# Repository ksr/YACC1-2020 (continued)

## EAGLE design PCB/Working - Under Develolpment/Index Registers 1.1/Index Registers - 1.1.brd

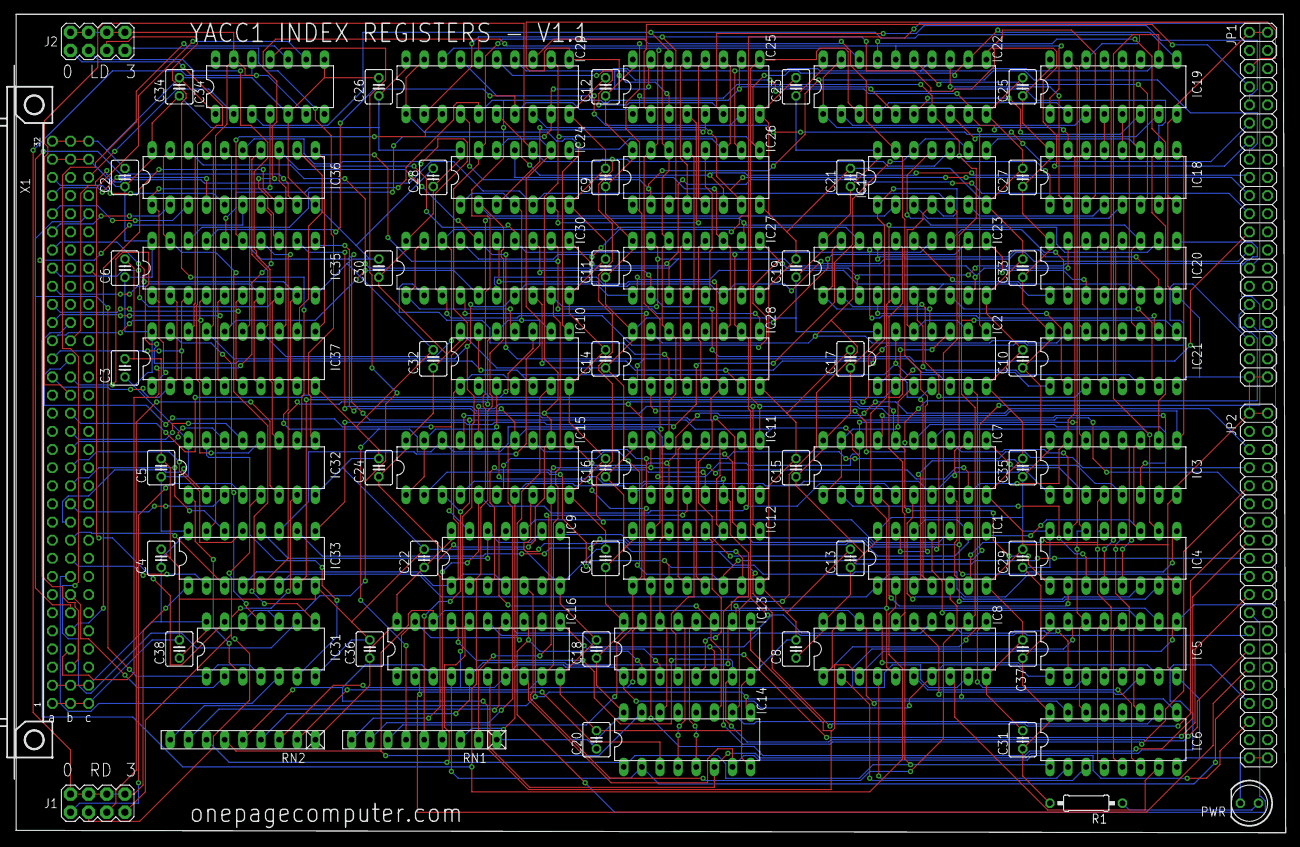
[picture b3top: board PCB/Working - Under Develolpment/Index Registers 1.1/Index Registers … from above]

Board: 2 copper layers, 177.8 x 114.6 mm, 83 parts (0 on the bottom side), 192 nets.

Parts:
C1, C2, C3, C4, C5, C6, C8, C9, C10, C11, C12, C13, C14, C15, C16, C17, C18, C19, C20, C21, C22, C23, C24, C25, C26, C27, C28, C29, C30, C31, C32, C33, C34, C35, C36, C37, C38: 0.1; C025-040X050
IC1, IC2, IC9, IC10, IC17, IC24, IC31: 74LS32N; DIL14
IC3, IC4, IC5, IC6, IC11, IC12, IC13, IC14, IC18, IC19, IC20, IC21, IC25, IC26, IC27, IC28: 74LS192N; DIL16
IC7, IC8, IC15, IC16, IC22, IC23, IC29, IC30: 74LS244N; DIL20
IC32, IC33: 74LS139N; DIL16
IC34: 4077N; DIL14
IC35, IC36, IC37: 74LS245N; DIL20
J1, J2: 2X4
JP1, JP2: 2X20
PWR: LED5MM
R1: 330; 0207/10
RN1, RN2: 10k; RN-9
X1: FABC96R

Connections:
-BUS-EN: IC31.1, IC31.4, X1.C28
-HL-SWAP: IC31.13, IC34.9, X1.C25
-LDSEL: IC33.15, IC34.6, IC34.13, J2.2, J2.4, J2.6, J2.8
-R0-LDSEL: IC9.9, IC9.12, IC33.12
-R0-RDSEL: IC9.1, IC9.4, IC10.1, IC10.4, IC33.4
-R1-LDSEL: IC24.9, IC24.12, IC33.11
-R1-RDSEL: IC10.9, IC10.12, IC24.1, IC24.4, IC33.5
-R2-LDSEL: IC1.9, IC1.12, IC33.10
-R2-RDSEL: IC1.1, IC1.4, IC2.1, IC2.4, IC33.6
-R3-LDSEL: IC17.9, IC17.12, IC33.9
-R3-RDSEL: IC2.9, IC2.12, IC17.1, IC17.4, IC33.7
-RDSEL: IC33.1, IC34.12, J1.2, J1.4, J1.6, J1.8
-REG-DN: IC1.5, IC9.5, IC17.5, IC24.5, X1.B21
-REG-FUNC-LD: IC31.5, X1.B8
-REG-FUNC-RD: IC31.2, X1.B7
-REG-LD-HI: IC1.13, IC9.13, IC17.13, IC24.13, X1.B20
-REG-LD-LO: IC1.10, IC9.10, IC17.10, IC24.10, X1.B18
-REG-RD-HI: IC2.5, IC2.13, IC10.5, IC10.13, X1.B19
-REG-RD-LO: IC2.2, IC2.10, IC10.2, IC10.10, X1.B17
-REG-UP: IC1.2, IC9.2, IC17.2, IC24.2, X1.B22
-RESET: IC34.2, X1.C30
-RLD0: IC32.12, J2.1
-RRD0: IC32.4, J1.1
ADATA0: IC3.15, IC7.9, IC11.15, IC15.9, IC18.15, IC22.9, IC25.15, IC29.9, IC35.18, RN1.2
ADATA1: IC3.1, IC7.7, IC11.1, IC15.7, IC18.1, IC22.7, IC25.1, IC29.7, IC35.17, RN1.3
ADATA2: IC3.10, IC7.5, IC11.10, IC15.5, IC18.10, IC22.5, IC25.10, IC29.5, IC35.16, RN1.4
ADATA3: IC3.9, IC7.3, IC11.9, IC15.3, IC18.9, IC22.3, IC25.9, IC29.3, IC35.15, RN1.5
ADATA4: IC4.15, IC7.18, IC12.15, IC15.18, IC19.15, IC22.18, IC26.15, IC29.18, IC35.14, RN1.6
ADATA5: IC4.1, IC7.16, IC12.1, IC15.16, IC19.1, IC22.16, IC26.1, IC29.16, IC35.13, RN1.7
ADATA6: IC4.10, IC7.14, IC12.10, IC15.14, IC19.10, IC22.14, IC26.10, IC29.14, IC35.12, RN1.8
ADATA7: IC4.9, IC7.12, IC12.9, IC15.12, IC19.9, IC22.12, IC26.9, IC29.12, IC35.11, RN1.9
ADATA8: IC5.15, IC8.9, IC13.15, IC16.9, IC20.15, IC23.9, IC27.15, IC30.9, IC36.18, IC37.18, RN2.2
ADATA9: IC5.1, IC8.7, IC13.1, IC16.7, IC20.1, IC23.7, IC27.1, IC30.7, IC36.17, IC37.17, RN2.3
ADATA10: IC5.10, IC8.5, IC13.10, IC16.5, IC20.10, IC23.5, IC27.10, IC30.5, IC36.16, IC37.16, RN2.4
ADATA11: IC5.9, IC8.3, IC13.9, IC16.3, IC20.9, IC23.3, IC27.9, IC30.3, IC36.15, IC37.15, RN2.5
ADATA12: IC6.15, IC8.18, IC14.15, IC16.18, IC21.15, IC23.18, IC28.15, IC30.18, IC36.14, IC37.14, RN2.6
ADATA13: IC6.1, IC8.16, IC14.1, IC16.16, IC21.1, IC23.16, IC28.1, IC30.16, IC36.13, IC37.13, RN2.7
ADATA14: IC6.10, IC8.14, IC14.10, IC16.14, IC21.10, IC23.14, IC28.10, IC30.14, IC36.12, IC37.12, RN2.8
ADATA15: IC6.9, IC8.12, IC14.9, IC16.12, IC21.9, IC23.12, IC28.9, IC30.12, IC36.11, IC37.11, RN2.9
BUS-DIR: IC34.4, IC35.1, IC36.1, IC37.1
DATA0: IC35.2, IC37.2, X1.A19
DATA1: IC35.3, IC37.3, X1.A20
DATA2: IC35.4, IC37.4, X1.A21
DATA3: IC35.5, IC37.5, X1.A22
DATA4: IC35.6, IC37.6, X1.A23
DATA5: IC35.7, IC37.7, X1.A24
DATA6: IC35.8, IC37.8, X1.A25
DATA7: IC35.9, IC37.9, X1.A26
DATA8: IC36.2, X1.A27
DATA9: IC36.3, X1.A28
DATA10: IC36.4, X1.A29
DATA11: IC36.5, X1.A30
DATA12: IC36.6, X1.B3
DATA13: IC36.7, X1.B4
DATA14: IC36.8, X1.B5
DATA15: IC36.9, X1.B6
GND: C1.2, C2.2, C3.2, C4.2, C5.2, C6.2, C8.2, C9.2, C10.2, C11.2, C12.2, C13.2, C14.2, C15.2, C16.2, C17.2, C18.2, C19.2, C20.2, C21.2, C22.2, C23.2, C24.2, C25.2, C26.2, C27.2, C28.2, C29.2, C30.2, C31.2, C32.2, C33.2, C34.2, C35.2, C36.2, C37.2, C38.2, IC1.7, IC2.7, IC3.8, IC4.8, IC5.8, IC6.8, IC7.10, IC8.10, IC9.7, IC10.7, IC11.8, IC12.8, IC13.8, IC14.8, IC15.10, IC16.10, IC17.7, IC18.8, IC19.8, IC20.8, IC21.8, IC22.10, IC23.10, IC24.7, IC25.8, IC26.8, IC27.8, IC28.8, IC29.10, IC30.10, IC31.7, IC32.8, IC33.8, IC34.1, IC34.5, IC34.8, IC35.10, IC36.10, IC37.10, JP1.1, JP1.2, JP1.39, JP1.40, JP2.1, JP2.2, JP2.39, JP2.40, PWR.K, X1.A1, X1.A32, X1.B1, X1.B32, X1.C1, X1.C32
IA-0: IC11.3, IC15.11, JP2.5
IA-1: IC11.2, IC15.13, JP2.7
IA-2: IC11.6, IC15.15, JP2.9
IA-3: IC11.7, IC15.17, JP2.11
IA-4: IC12.3, IC15.2, JP2.13
IA-5: IC12.2, IC15.4, JP2.15
IA-6: IC12.6, IC15.6, JP2.17
IA-7: IC12.7, IC15.8, JP2.19
IA-8: IC13.3, IC16.11, JP2.21
IA-9: IC13.2, IC16.13, JP2.23
IA-10: IC13.6, IC16.15, JP2.25
IA-11: IC13.7, IC16.17, JP2.27
IA-12: IC14.3, IC16.2, JP2.29
IA-13: IC14.2, IC16.4, JP2.31
IA-14: IC14.6, IC16.6, JP2.33
IA-15: IC14.7, IC16.8, JP2.35
IC-0: IC25.3, IC29.11, JP1.5
IC-1: IC25.2, IC29.13, JP1.7
IC-2: IC25.6, IC29.15, JP1.9
IC-3: IC25.7, IC29.17, JP1.11
IC-4: IC26.3, IC29.2, JP1.13
IC-5: IC26.2, IC29.4, JP1.15
IC-6: IC26.6, IC29.6, JP1.17
IC-7: IC26.7, IC29.8, JP1.19
IC-8: IC27.3, IC30.11, JP1.21
IC-9: IC27.2, IC30.13, JP1.23
IC-10: IC27.6, IC30.15, JP1.25
IC-11: IC27.7, IC30.17, JP1.27
IC-12: IC28.3, IC30.2
IC-13: IC28.2, IC30.4, JP1.31
IC-14: IC28.6, IC30.6, JP1.33
IC-15: IC28.7, IC30.8, JP1.35
unnamed: IC31.8, IC35.19, IC36.19
unnamed: IC25.13, IC26.4
unnamed: IC25.12, IC26.5
unnamed: IC26.13, IC27.4
unnamed: IC26.12, IC27.5
unnamed: IC27.13, IC28.4
unnamed: IC27.12, IC28.5
unnamed: IC24.8, IC25.11, IC26.11
unnamed: IC24.3, IC25.5
unnamed: IC3.13, IC4.4
unnamed: IC3.12, IC4.5
unnamed: IC4.13, IC5.4
unnamed: IC4.12, IC5.5
unnamed: IC5.13, IC6.4
unnamed: IC5.12, IC6.5
unnamed: IC1.8, IC3.11, IC4.11
unnamed: IC1.3, IC3.5
unnamed: IC1.6, IC3.4
unnamed: IC31.3, IC32.1
unnamed: IC2.3, IC7.1, IC7.19
unnamed: IC2.6, IC8.1, IC8.19
unnamed: IC1.11, IC5.11, IC6.11
unnamed: IC24.6, IC25.4
unnamed: IC31.6, IC32.15
unnamed: IC10.8, IC29.1, IC29.19
unnamed: IC10.11, IC30.1, IC30.19
unnamed: IC24.11, IC27.11, IC28.11
unnamed: IC11.13, IC12.4
unnamed: IC11.12, IC12.5
unnamed: IC12.13, IC13.4
unnamed: IC12.12, IC13.5
unnamed: IC13.13, IC14.4
unnamed: IC13.12, IC14.5
unnamed: IC9.8, IC11.11, IC12.11
unnamed: IC9.3, IC11.5
unnamed: IC9.6, IC11.4
unnamed: IC31.11, IC37.19
unnamed: IC10.3, IC15.1, IC15.19
unnamed: IC10.6, IC16.1, IC16.19
unnamed: IC9.11, IC13.11, IC14.11
unnamed: IC31.9, IC34.10
unnamed: IC31.10, IC31.12, IC34.11
unnamed: IC32.5, J1.3
unnamed: PWR.A, R1.1
unnamed: IC32.6, J1.5
unnamed: IC32.7, J1.7
unnamed: IC32.11, J2.3
unnamed: IC32.10, J2.5
unnamed: IC32.9, J2.7
unnamed: IC18.13, IC19.4
unnamed: IC18.12, IC19.5
unnamed: IC19.13, IC20.4
unnamed: IC19.12, IC20.5
unnamed: IC20.13, IC21.4
unnamed: IC20.12, IC21.5
unnamed: IC17.8, IC18.11, IC19.11
unnamed: IC17.3, IC18.5
unnamed: IC17.6, IC18.4
unnamed: IC18.3, IC22.11
unnamed: IC18.2, IC22.13
unnamed: IC18.6, IC22.15
unnamed: IC18.7, IC22.17
unnamed: IC2.8, IC22.1, IC22.19
unnamed: IC2.11, IC23.1, IC23.19
unnamed: IC17.11, IC20.11, IC21.11
unnamed: IC19.3, IC22.2
unnamed: IC19.2, IC22.4
unnamed: IC19.6, IC22.6
unnamed: IC19.7, IC22.8
unnamed: IC20.3, IC23.11
unnamed: IC20.2, IC23.13
unnamed: IC20.6, IC23.15
unnamed: IC20.7, IC23.17
unnamed: IC21.3, IC23.2
unnamed: IC21.2, IC23.4
unnamed: IC21.6, IC23.6
unnamed: IC21.7, IC23.8
unnamed: IC3.3, IC7.11
unnamed: IC3.2, IC7.13
unnamed: IC3.6, IC7.15
unnamed: IC3.7, IC7.17
unnamed: IC4.3, IC7.2
unnamed: IC4.2, IC7.4
unnamed: IC4.6, IC7.6
unnamed: IC4.7, IC7.8
unnamed: IC5.3, IC8.11
unnamed: IC5.2, IC8.13
unnamed: IC5.6, IC8.15
unnamed: IC5.7, IC8.17
unnamed: IC6.3, IC8.2
unnamed: IC6.2, IC8.4
unnamed: IC6.6, IC8.6
unnamed: IC6.7, IC8.8
REG-LD-ID0: IC33.14, X1.B13
REG-LD-ID1: IC33.13, X1.B14
REG-LD-ID2: IC32.14, X1.B15
REG-LD-ID3: IC32.13, X1.B16
REG-RD-ID0: IC33.2, X1.B9
REG-RD-ID1: IC33.3, X1.B10
REG-RD-ID2: IC32.2, X1.B11
REG-RD-ID3: IC32.3, X1.B12
RESET: IC3.14, IC4.14, IC5.14, IC6.14, IC11.14, IC12.14, IC13.14, IC14.14, IC18.14, IC19.14, IC20.14, IC21.14, IC25.14, IC26.14, IC27.14, IC28.14, IC34.3
VCC: C1.1, C2.1, C3.1, C4.1, C5.1, C6.1, C8.1, C9.1, C10.1, C11.1, C12.1, C13.1, C14.1, C15.1, C16.1, C17.1, C18.1, C19.1, C20.1, C21.1, C22.1, C23.1, C24.1, C25.1, C26.1, C27.1, C28.1, C29.1, C30.1, C31.1, C32.1, C33.1, C34.1, C35.1, C36.1, C37.1, C38.1, IC1.14, IC2.14, IC3.16, IC4.16, IC5.16, IC6.16, IC7.20, IC8.20, IC9.14, IC10.14, IC11.16, IC12.16, IC13.16, IC14.16, IC15.20, IC16.20, IC17.14, IC18.16, IC19.16, IC20.16, IC21.16, IC22.20, IC23.20, IC24.14, IC25.16, IC26.16, IC27.16, IC28.16, IC29.20, IC30.20, IC31.14, IC32.16, IC33.16, IC35.20, IC36.20, IC37.20, R1.2, RN1.1, RN2.1, X1.A2, X1.A31, X1.B2, X1.B31, X1.C2, X1.C31

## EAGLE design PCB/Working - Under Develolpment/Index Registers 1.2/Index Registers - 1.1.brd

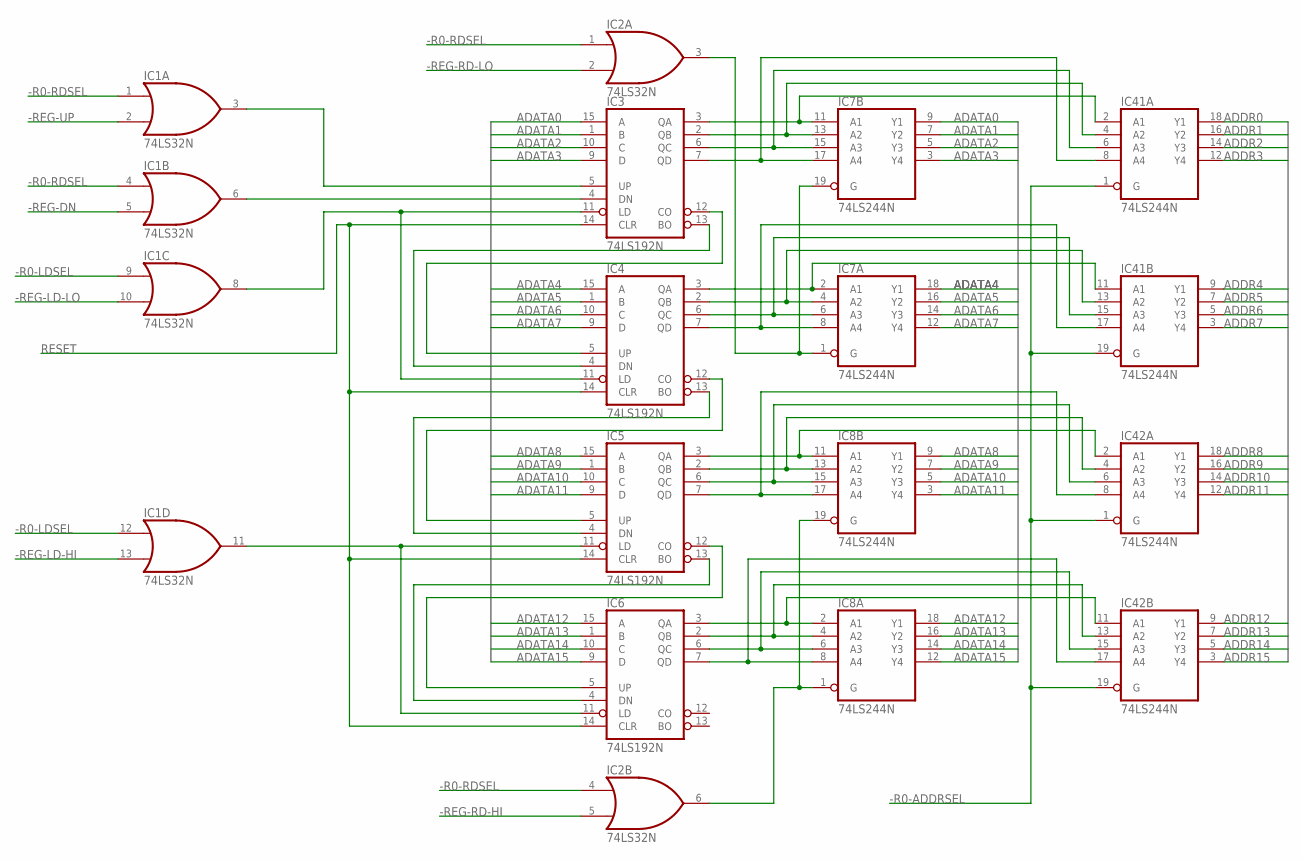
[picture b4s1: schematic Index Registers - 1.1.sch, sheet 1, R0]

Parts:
IC1, IC2: 74LS32N; DIL14
IC3, IC4, IC5, IC6: 74LS192N; DIL16
IC7, IC8, IC41, IC42: 74LS244N; DIL20

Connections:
-R0-ADDRSEL: IC41.1 (G), IC41.19 (G), IC42.1 (G), IC42.19 (G); also elsewhere on the board
-R0-LDSEL: IC1.9 (I0), IC1.12 (I0); also elsewhere on the board
-R0-RDSEL: IC1.1 (I0), IC1.4 (I0), IC2.1 (I0), IC2.4 (I0); also elsewhere on the board
-REG-DN: IC1.5 (I1); also elsewhere on the board
-REG-LD-HI: IC1.13 (I1); also elsewhere on the board
-REG-LD-LO: IC1.10 (I1); also elsewhere on the board
-REG-RD-HI: IC2.5 (I1); also elsewhere on the board
-REG-RD-LO: IC2.2 (I1); also elsewhere on the board
-REG-UP: IC1.2 (I1); also elsewhere on the board
ADATA0: IC3.15 (A), IC7.9 (Y1); also elsewhere on the board
ADATA1: IC3.1 (B), IC7.7 (Y2); also elsewhere on the board
ADATA2: IC3.10 (C), IC7.5 (Y3); also elsewhere on the board
ADATA3: IC3.9 (D), IC7.3 (Y4); also elsewhere on the board
ADATA4: IC4.15 (A), IC7.18 (Y1); also elsewhere on the board
ADATA5: IC4.1 (B), IC7.16 (Y2); also elsewhere on the board
ADATA6: IC4.10 (C), IC7.14 (Y3); also elsewhere on the board
ADATA7: IC4.9 (D), IC7.12 (Y4); also elsewhere on the board
ADATA8: IC5.15 (A), IC8.9 (Y1); also elsewhere on the board
ADATA9: IC5.1 (B), IC8.7 (Y2); also elsewhere on the board
ADATA10: IC5.10 (C), IC8.5 (Y3); also elsewhere on the board
ADATA11: IC5.9 (D), IC8.3 (Y4); also elsewhere on the board
ADATA12: IC6.15 (A), IC8.18 (Y1); also elsewhere on the board
ADATA13: IC6.1 (B), IC8.16 (Y2); also elsewhere on the board
ADATA14: IC6.10 (C), IC8.14 (Y3); also elsewhere on the board
ADATA15: IC6.9 (D), IC8.12 (Y4); also elsewhere on the board
ADDR0: IC41.18 (Y1); also elsewhere on the board
ADDR1: IC41.16 (Y2); also elsewhere on the board
ADDR2: IC41.14 (Y3); also elsewhere on the board
ADDR3: IC41.12 (Y4); also elsewhere on the board
ADDR4: IC41.9 (Y1); also elsewhere on the board
ADDR5: IC41.7 (Y2); also elsewhere on the board
ADDR6: IC41.5 (Y3); also elsewhere on the board
ADDR7: IC41.3 (Y4); also elsewhere on the board
ADDR8: IC42.18 (Y1); also elsewhere on the board
ADDR9: IC42.16 (Y2); also elsewhere on the board
ADDR10: IC42.14 (Y3); also elsewhere on the board
ADDR11: IC42.12 (Y4); also elsewhere on the board
ADDR12: IC42.9 (Y1); also elsewhere on the board
ADDR13: IC42.7 (Y2); also elsewhere on the board
ADDR14: IC42.5 (Y3); also elsewhere on the board
ADDR15: IC42.3 (Y4); also elsewhere on the board
GND: IC1.7 (GND), IC2.7 (GND), IC3.8 (GND), IC4.8 (GND), IC5.8 (GND), IC6.8 (GND), IC7.10 (GND), IC8.10 (GND), IC41.10 (GND), IC42.10 (GND); also elsewhere on the board
unnamed: IC3.13 (BO), IC4.4 (DN)
unnamed: IC3.12 (CO), IC4.5 (UP)
unnamed: IC4.13 (BO), IC5.4 (DN)
unnamed: IC4.12 (CO), IC5.5 (UP)
unnamed: IC5.13 (BO), IC6.4 (DN)
unnamed: IC5.12 (CO), IC6.5 (UP)
unnamed: IC1.8 (O), IC3.11 (LD), IC4.11 (LD)
unnamed: IC1.3 (O), IC3.5 (UP)
unnamed: IC1.6 (O), IC3.4 (DN)
unnamed: IC2.3 (O), IC7.1 (G), IC7.19 (G)
unnamed: IC2.6 (O), IC8.1 (G), IC8.19 (G)
unnamed: IC1.11 (O), IC5.11 (LD), IC6.11 (LD)
unnamed: IC3.3 (QA), IC7.11 (A1), IC41.2 (A1)
unnamed: IC3.2 (QB), IC7.13 (A2), IC41.4 (A2)
unnamed: IC3.6 (QC), IC7.15 (A3), IC41.6 (A3)
unnamed: IC3.7 (QD), IC7.17 (A4), IC41.8 (A4)
unnamed: IC4.3 (QA), IC7.2 (A1), IC41.11 (A1)
unnamed: IC4.2 (QB), IC7.4 (A2), IC41.13 (A2)
unnamed: IC4.6 (QC), IC7.6 (A3), IC41.15 (A3)
unnamed: IC4.7 (QD), IC7.8 (A4), IC41.17 (A4)
unnamed: IC5.3 (QA), IC8.11 (A1), IC42.2 (A1)
unnamed: IC5.2 (QB), IC8.13 (A2), IC42.4 (A2)
unnamed: IC5.6 (QC), IC8.15 (A3), IC42.6 (A3)
unnamed: IC5.7 (QD), IC8.17 (A4), IC42.8 (A4)
unnamed: IC6.3 (QA), IC8.2 (A1), IC42.11 (A1)
unnamed: IC6.2 (QB), IC8.4 (A2), IC42.13 (A2)
unnamed: IC6.6 (QC), IC8.6 (A3), IC42.15 (A3)
unnamed: IC6.7 (QD), IC8.8 (A4), IC42.17 (A4)
RESET: IC3.14 (CLR), IC4.14 (CLR), IC5.14 (CLR), IC6.14 (CLR); also elsewhere on the board
VCC: IC1.14 (VCC), IC2.14 (VCC), IC3.16 (VCC), IC4.16 (VCC), IC5.16 (VCC), IC6.16 (VCC), IC7.20 (VCC), IC8.20 (VCC), IC41.20 (VCC), IC42.20 (VCC); also elsewhere on the board

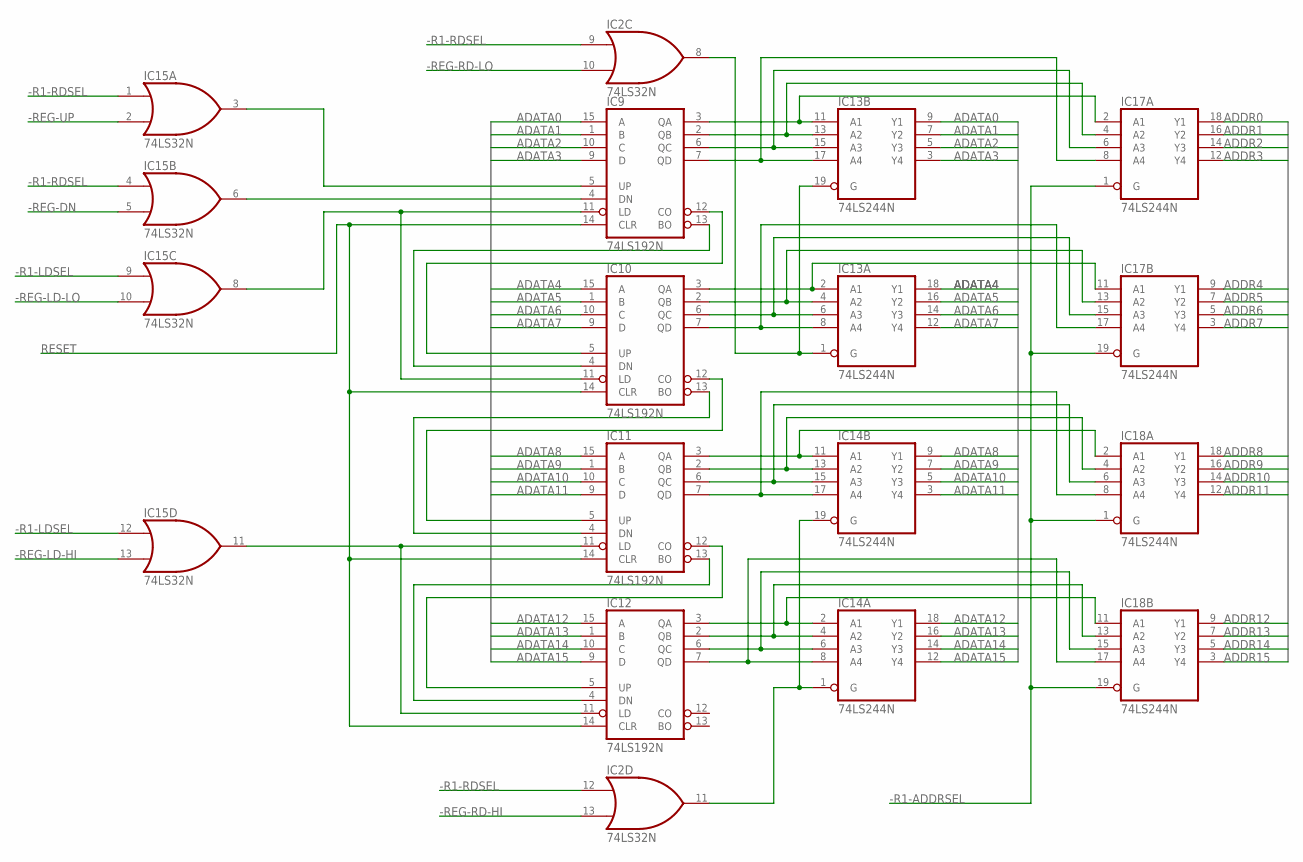
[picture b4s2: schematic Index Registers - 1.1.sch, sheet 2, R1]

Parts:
IC2, IC15: 74LS32N; DIL14
IC9, IC10, IC11, IC12: 74LS192N; DIL16
IC13, IC14, IC17, IC18: 74LS244N; DIL20

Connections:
-R1-ADDRSEL: IC17.1 (G), IC17.19 (G), IC18.1 (G), IC18.19 (G); also elsewhere on the board
-R1-LDSEL: IC15.9 (I0), IC15.12 (I0); also elsewhere on the board
-R1-RDSEL: IC2.9 (I0), IC2.12 (I0), IC15.1 (I0), IC15.4 (I0); also elsewhere on the board
-REG-DN: IC15.5 (I1); also elsewhere on the board
-REG-LD-HI: IC15.13 (I1); also elsewhere on the board
-REG-LD-LO: IC15.10 (I1); also elsewhere on the board
-REG-RD-HI: IC2.13 (I1); also elsewhere on the board
-REG-RD-LO: IC2.10 (I1); also elsewhere on the board
-REG-UP: IC15.2 (I1); also elsewhere on the board
ADATA0: IC9.15 (A), IC13.9 (Y1); also elsewhere on the board
ADATA1: IC9.1 (B), IC13.7 (Y2); also elsewhere on the board
ADATA2: IC9.10 (C), IC13.5 (Y3); also elsewhere on the board
ADATA3: IC9.9 (D), IC13.3 (Y4); also elsewhere on the board
ADATA4: IC10.15 (A), IC13.18 (Y1); also elsewhere on the board
ADATA5: IC10.1 (B), IC13.16 (Y2); also elsewhere on the board
ADATA6: IC10.10 (C), IC13.14 (Y3); also elsewhere on the board
ADATA7: IC10.9 (D), IC13.12 (Y4); also elsewhere on the board
ADATA8: IC11.15 (A), IC14.9 (Y1); also elsewhere on the board
ADATA9: IC11.1 (B), IC14.7 (Y2); also elsewhere on the board
ADATA10: IC11.10 (C), IC14.5 (Y3); also elsewhere on the board
ADATA11: IC11.9 (D), IC14.3 (Y4); also elsewhere on the board
ADATA12: IC12.15 (A), IC14.18 (Y1); also elsewhere on the board
ADATA13: IC12.1 (B), IC14.16 (Y2); also elsewhere on the board
ADATA14: IC12.10 (C), IC14.14 (Y3); also elsewhere on the board
ADATA15: IC12.9 (D), IC14.12 (Y4); also elsewhere on the board
ADDR0: IC17.18 (Y1); also elsewhere on the board
ADDR1: IC17.16 (Y2); also elsewhere on the board
ADDR2: IC17.14 (Y3); also elsewhere on the board
ADDR3: IC17.12 (Y4); also elsewhere on the board
ADDR4: IC17.9 (Y1); also elsewhere on the board
ADDR5: IC17.7 (Y2); also elsewhere on the board
ADDR6: IC17.5 (Y3); also elsewhere on the board
ADDR7: IC17.3 (Y4); also elsewhere on the board
ADDR8: IC18.18 (Y1); also elsewhere on the board
ADDR9: IC18.16 (Y2); also elsewhere on the board
ADDR10: IC18.14 (Y3); also elsewhere on the board
ADDR11: IC18.12 (Y4); also elsewhere on the board
ADDR12: IC18.9 (Y1); also elsewhere on the board
ADDR13: IC18.7 (Y2); also elsewhere on the board
ADDR14: IC18.5 (Y3); also elsewhere on the board
ADDR15: IC18.3 (Y4); also elsewhere on the board
GND: IC2.7 (GND), IC9.8 (GND), IC10.8 (GND), IC11.8 (GND), IC12.8 (GND), IC13.10 (GND), IC14.10 (GND), IC15.7 (GND), IC17.10 (GND), IC18.10 (GND); also elsewhere on the board
unnamed: IC9.13 (BO), IC10.4 (DN)
unnamed: IC9.12 (CO), IC10.5 (UP)
unnamed: IC10.13 (BO), IC11.4 (DN)
unnamed: IC10.12 (CO), IC11.5 (UP)
unnamed: IC11.13 (BO), IC12.4 (DN)
unnamed: IC11.12 (CO), IC12.5 (UP)
unnamed: IC9.11 (LD), IC10.11 (LD), IC15.8 (O)
unnamed: IC9.5 (UP), IC15.3 (O)
unnamed: IC9.4 (DN), IC15.6 (O)
unnamed: IC2.8 (O), IC13.1 (G), IC13.19 (G)
unnamed: IC2.11 (O), IC14.1 (G), IC14.19 (G)
unnamed: IC11.11 (LD), IC12.11 (LD), IC15.11 (O)
unnamed: IC9.3 (QA), IC13.11 (A1), IC17.2 (A1)
unnamed: IC9.2 (QB), IC13.13 (A2), IC17.4 (A2)
unnamed: IC9.6 (QC), IC13.15 (A3), IC17.6 (A3)
unnamed: IC9.7 (QD), IC13.17 (A4), IC17.8 (A4)
unnamed: IC10.3 (QA), IC13.2 (A1), IC17.11 (A1)
unnamed: IC10.2 (QB), IC13.4 (A2), IC17.13 (A2)
unnamed: IC10.6 (QC), IC13.6 (A3), IC17.15 (A3)
unnamed: IC10.7 (QD), IC13.8 (A4), IC17.17 (A4)
unnamed: IC11.3 (QA), IC14.11 (A1), IC18.2 (A1)
unnamed: IC11.2 (QB), IC14.13 (A2), IC18.4 (A2)
unnamed: IC11.6 (QC), IC14.15 (A3), IC18.6 (A3)
unnamed: IC11.7 (QD), IC14.17 (A4), IC18.8 (A4)
unnamed: IC12.3 (QA), IC14.2 (A1), IC18.11 (A1)
unnamed: IC12.2 (QB), IC14.4 (A2), IC18.13 (A2)
unnamed: IC12.6 (QC), IC14.6 (A3), IC18.15 (A3)
unnamed: IC12.7 (QD), IC14.8 (A4), IC18.17 (A4)
RESET: IC9.14 (CLR), IC10.14 (CLR), IC11.14 (CLR), IC12.14 (CLR); also elsewhere on the board
VCC: IC2.14 (VCC), IC9.16 (VCC), IC10.16 (VCC), IC11.16 (VCC), IC12.16 (VCC), IC13.20 (VCC), IC14.20 (VCC), IC15.14 (VCC), IC17.20 (VCC), IC18.20 (VCC); also elsewhere on the board

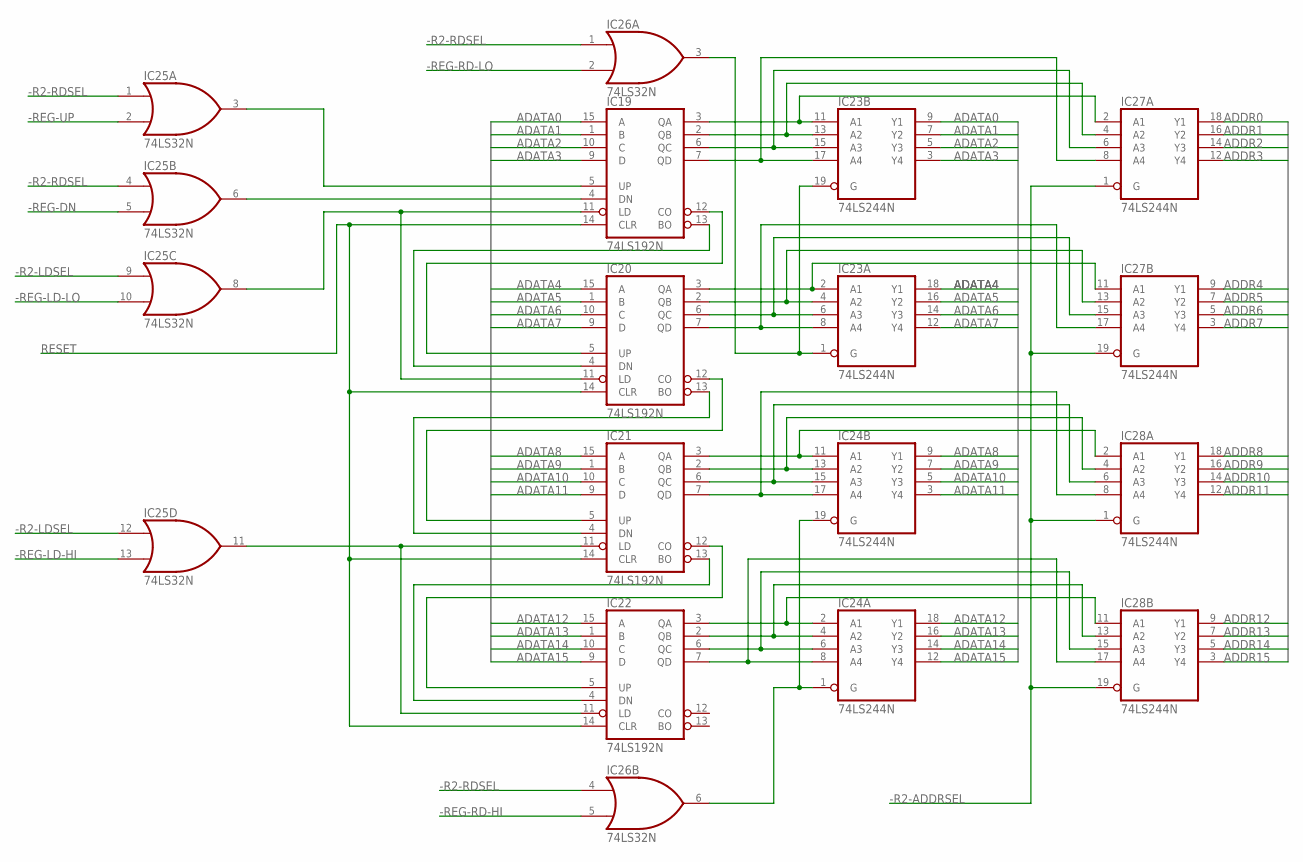
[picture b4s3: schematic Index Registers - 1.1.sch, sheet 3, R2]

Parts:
IC19, IC20, IC21, IC22: 74LS192N; DIL16
IC23, IC24, IC27, IC28: 74LS244N; DIL20
IC25, IC26: 74LS32N; DIL14

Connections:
-R2-ADDRSEL: IC27.1 (G), IC27.19 (G), IC28.1 (G), IC28.19 (G); also elsewhere on the board
-R2-LDSEL: IC25.9 (I0), IC25.12 (I0); also elsewhere on the board
-R2-RDSEL: IC25.1 (I0), IC25.4 (I0), IC26.1 (I0), IC26.4 (I0); also elsewhere on the board
-REG-DN: IC25.5 (I1); also elsewhere on the board
-REG-LD-HI: IC25.13 (I1); also elsewhere on the board
-REG-LD-LO: IC25.10 (I1); also elsewhere on the board
-REG-RD-HI: IC26.5 (I1); also elsewhere on the board
-REG-RD-LO: IC26.2 (I1); also elsewhere on the board
-REG-UP: IC25.2 (I1); also elsewhere on the board
ADATA0: IC19.15 (A), IC23.9 (Y1); also elsewhere on the board
ADATA1: IC19.1 (B), IC23.7 (Y2); also elsewhere on the board
ADATA2: IC19.10 (C), IC23.5 (Y3); also elsewhere on the board
ADATA3: IC19.9 (D), IC23.3 (Y4); also elsewhere on the board
ADATA4: IC20.15 (A), IC23.18 (Y1); also elsewhere on the board
ADATA5: IC20.1 (B), IC23.16 (Y2); also elsewhere on the board
ADATA6: IC20.10 (C), IC23.14 (Y3); also elsewhere on the board
ADATA7: IC20.9 (D), IC23.12 (Y4); also elsewhere on the board
ADATA8: IC21.15 (A), IC24.9 (Y1); also elsewhere on the board
ADATA9: IC21.1 (B), IC24.7 (Y2); also elsewhere on the board
ADATA10: IC21.10 (C), IC24.5 (Y3); also elsewhere on the board
ADATA11: IC21.9 (D), IC24.3 (Y4); also elsewhere on the board
ADATA12: IC22.15 (A), IC24.18 (Y1); also elsewhere on the board
ADATA13: IC22.1 (B), IC24.16 (Y2); also elsewhere on the board
ADATA14: IC22.10 (C), IC24.14 (Y3); also elsewhere on the board
ADATA15: IC22.9 (D), IC24.12 (Y4); also elsewhere on the board
ADDR0: IC27.18 (Y1); also elsewhere on the board
ADDR1: IC27.16 (Y2); also elsewhere on the board
ADDR2: IC27.14 (Y3); also elsewhere on the board
ADDR3: IC27.12 (Y4); also elsewhere on the board
ADDR4: IC27.9 (Y1); also elsewhere on the board
ADDR5: IC27.7 (Y2); also elsewhere on the board
ADDR6: IC27.5 (Y3); also elsewhere on the board
ADDR7: IC27.3 (Y4); also elsewhere on the board
ADDR8: IC28.18 (Y1); also elsewhere on the board
ADDR9: IC28.16 (Y2); also elsewhere on the board
ADDR10: IC28.14 (Y3); also elsewhere on the board
ADDR11: IC28.12 (Y4); also elsewhere on the board
ADDR12: IC28.9 (Y1); also elsewhere on the board
ADDR13: IC28.7 (Y2); also elsewhere on the board
ADDR14: IC28.5 (Y3); also elsewhere on the board
ADDR15: IC28.3 (Y4); also elsewhere on the board
GND: IC19.8 (GND), IC20.8 (GND), IC21.8 (GND), IC22.8 (GND), IC23.10 (GND), IC24.10 (GND), IC25.7 (GND), IC26.7 (GND), IC27.10 (GND), IC28.10 (GND); also elsewhere on the board
unnamed: IC19.13 (BO), IC20.4 (DN)
unnamed: IC19.12 (CO), IC20.5 (UP)
unnamed: IC20.13 (BO), IC21.4 (DN)
unnamed: IC20.12 (CO), IC21.5 (UP)
unnamed: IC21.13 (BO), IC22.4 (DN)
unnamed: IC21.12 (CO), IC22.5 (UP)
unnamed: IC19.11 (LD), IC20.11 (LD), IC25.8 (O)
unnamed: IC19.5 (UP), IC25.3 (O)
unnamed: IC19.4 (DN), IC25.6 (O)
unnamed: IC23.1 (G), IC23.19 (G), IC26.3 (O)
unnamed: IC24.1 (G), IC24.19 (G), IC26.6 (O)
unnamed: IC21.11 (LD), IC22.11 (LD), IC25.11 (O)
unnamed: IC19.3 (QA), IC23.11 (A1), IC27.2 (A1)
unnamed: IC19.2 (QB), IC23.13 (A2), IC27.4 (A2)
unnamed: IC19.6 (QC), IC23.15 (A3), IC27.6 (A3)
unnamed: IC19.7 (QD), IC23.17 (A4), IC27.8 (A4)
unnamed: IC20.3 (QA), IC23.2 (A1), IC27.11 (A1)
unnamed: IC20.2 (QB), IC23.4 (A2), IC27.13 (A2)
unnamed: IC20.6 (QC), IC23.6 (A3), IC27.15 (A3)
unnamed: IC20.7 (QD), IC23.8 (A4), IC27.17 (A4)
unnamed: IC21.3 (QA), IC24.11 (A1), IC28.2 (A1)
unnamed: IC21.2 (QB), IC24.13 (A2), IC28.4 (A2)
unnamed: IC21.6 (QC), IC24.15 (A3), IC28.6 (A3)
unnamed: IC21.7 (QD), IC24.17 (A4), IC28.8 (A4)
unnamed: IC22.3 (QA), IC24.2 (A1), IC28.11 (A1)
unnamed: IC22.2 (QB), IC24.4 (A2), IC28.13 (A2)
unnamed: IC22.6 (QC), IC24.6 (A3), IC28.15 (A3)
unnamed: IC22.7 (QD), IC24.8 (A4), IC28.17 (A4)
RESET: IC19.14 (CLR), IC20.14 (CLR), IC21.14 (CLR), IC22.14 (CLR); also elsewhere on the board
VCC: IC19.16 (VCC), IC20.16 (VCC), IC21.16 (VCC), IC22.16 (VCC), IC23.20 (VCC), IC24.20 (VCC), IC25.14 (VCC), IC26.14 (VCC), IC27.20 (VCC), IC28.20 (VCC); also elsewhere on the board

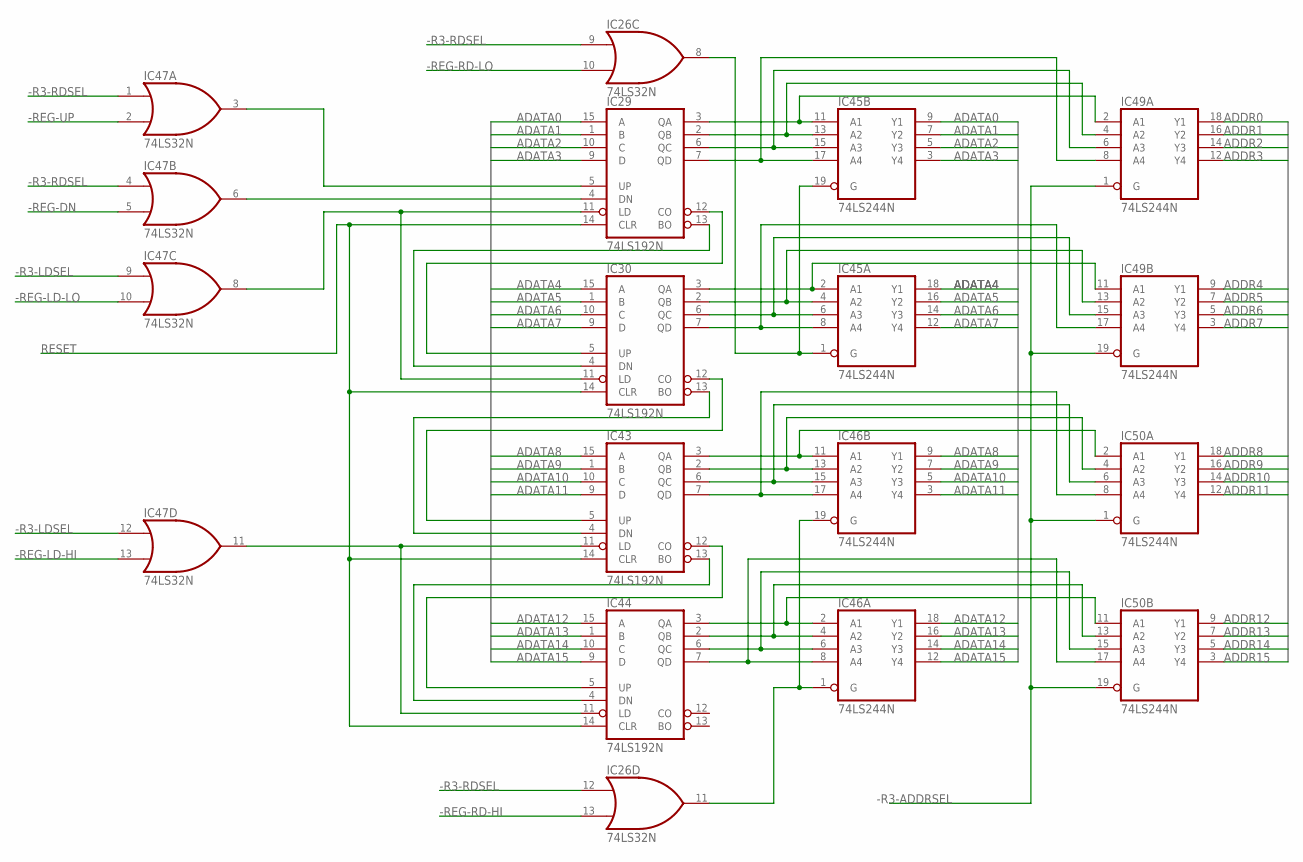
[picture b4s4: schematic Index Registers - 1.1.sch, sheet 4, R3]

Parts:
IC26, IC47: 74LS32N; DIL14
IC29, IC30, IC43, IC44: 74LS192N; DIL16
IC45, IC46, IC49, IC50: 74LS244N; DIL20

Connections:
-R3-ADDRSEL: IC49.1 (G), IC49.19 (G), IC50.1 (G), IC50.19 (G); also elsewhere on the board
-R3-LDSEL: IC47.9 (I0), IC47.12 (I0); also elsewhere on the board
-R3-RDSEL: IC26.9 (I0), IC26.12 (I0), IC47.1 (I0), IC47.4 (I0); also elsewhere on the board
-REG-DN: IC47.5 (I1); also elsewhere on the board
-REG-LD-HI: IC47.13 (I1); also elsewhere on the board
-REG-LD-LO: IC47.10 (I1); also elsewhere on the board
-REG-RD-HI: IC26.13 (I1); also elsewhere on the board
-REG-RD-LO: IC26.10 (I1); also elsewhere on the board
-REG-UP: IC47.2 (I1); also elsewhere on the board
ADATA0: IC29.15 (A), IC45.9 (Y1); also elsewhere on the board
ADATA1: IC29.1 (B), IC45.7 (Y2); also elsewhere on the board
ADATA2: IC29.10 (C), IC45.5 (Y3); also elsewhere on the board
ADATA3: IC29.9 (D), IC45.3 (Y4); also elsewhere on the board
ADATA4: IC30.15 (A), IC45.18 (Y1); also elsewhere on the board
ADATA5: IC30.1 (B), IC45.16 (Y2); also elsewhere on the board
ADATA6: IC30.10 (C), IC45.14 (Y3); also elsewhere on the board
ADATA7: IC30.9 (D), IC45.12 (Y4); also elsewhere on the board
ADATA8: IC43.15 (A), IC46.9 (Y1); also elsewhere on the board
ADATA9: IC43.1 (B), IC46.7 (Y2); also elsewhere on the board
ADATA10: IC43.10 (C), IC46.5 (Y3); also elsewhere on the board
ADATA11: IC43.9 (D), IC46.3 (Y4); also elsewhere on the board
ADATA12: IC44.15 (A), IC46.18 (Y1); also elsewhere on the board
ADATA13: IC44.1 (B), IC46.16 (Y2); also elsewhere on the board
ADATA14: IC44.10 (C), IC46.14 (Y3); also elsewhere on the board
ADATA15: IC44.9 (D), IC46.12 (Y4); also elsewhere on the board
ADDR0: IC49.18 (Y1); also elsewhere on the board
ADDR1: IC49.16 (Y2); also elsewhere on the board
ADDR2: IC49.14 (Y3); also elsewhere on the board
ADDR3: IC49.12 (Y4); also elsewhere on the board
ADDR4: IC49.9 (Y1); also elsewhere on the board
ADDR5: IC49.7 (Y2); also elsewhere on the board
ADDR6: IC49.5 (Y3); also elsewhere on the board
ADDR7: IC49.3 (Y4); also elsewhere on the board
ADDR8: IC50.18 (Y1); also elsewhere on the board
ADDR9: IC50.16 (Y2); also elsewhere on the board
ADDR10: IC50.14 (Y3); also elsewhere on the board
ADDR11: IC50.12 (Y4); also elsewhere on the board
ADDR12: IC50.9 (Y1); also elsewhere on the board
ADDR13: IC50.7 (Y2); also elsewhere on the board
ADDR14: IC50.5 (Y3); also elsewhere on the board
ADDR15: IC50.3 (Y4); also elsewhere on the board
GND: IC26.7 (GND), IC29.8 (GND), IC30.8 (GND), IC43.8 (GND), IC44.8 (GND), IC45.10 (GND), IC46.10 (GND), IC47.7 (GND), IC49.10 (GND), IC50.10 (GND); also elsewhere on the board
unnamed: IC29.13 (BO), IC30.4 (DN)
unnamed: IC29.12 (CO), IC30.5 (UP)
unnamed: IC30.13 (BO), IC43.4 (DN)
unnamed: IC30.12 (CO), IC43.5 (UP)
unnamed: IC43.13 (BO), IC44.4 (DN)
unnamed: IC43.12 (CO), IC44.5 (UP)
unnamed: IC29.11 (LD), IC30.11 (LD), IC47.8 (O)
unnamed: IC29.5 (UP), IC47.3 (O)
unnamed: IC29.4 (DN), IC47.6 (O)
unnamed: IC26.8 (O), IC45.1 (G), IC45.19 (G)
unnamed: IC26.11 (O), IC46.1 (G), IC46.19 (G)
unnamed: IC43.11 (LD), IC44.11 (LD), IC47.11 (O)
unnamed: IC29.3 (QA), IC45.11 (A1), IC49.2 (A1)
unnamed: IC29.2 (QB), IC45.13 (A2), IC49.4 (A2)
unnamed: IC29.6 (QC), IC45.15 (A3), IC49.6 (A3)
unnamed: IC29.7 (QD), IC45.17 (A4), IC49.8 (A4)
unnamed: IC30.3 (QA), IC45.2 (A1), IC49.11 (A1)
unnamed: IC30.2 (QB), IC45.4 (A2), IC49.13 (A2)
unnamed: IC30.6 (QC), IC45.6 (A3), IC49.15 (A3)
unnamed: IC30.7 (QD), IC45.8 (A4), IC49.17 (A4)
unnamed: IC43.3 (QA), IC46.11 (A1), IC50.2 (A1)
unnamed: IC43.2 (QB), IC46.13 (A2), IC50.4 (A2)
unnamed: IC43.6 (QC), IC46.15 (A3), IC50.6 (A3)
unnamed: IC43.7 (QD), IC46.17 (A4), IC50.8 (A4)
unnamed: IC44.3 (QA), IC46.2 (A1), IC50.11 (A1)
unnamed: IC44.2 (QB), IC46.4 (A2), IC50.13 (A2)
unnamed: IC44.6 (QC), IC46.6 (A3), IC50.15 (A3)
unnamed: IC44.7 (QD), IC46.8 (A4), IC50.17 (A4)
RESET: IC29.14 (CLR), IC30.14 (CLR), IC43.14 (CLR), IC44.14 (CLR); also elsewhere on the board
VCC: IC26.14 (VCC), IC29.16 (VCC), IC30.16 (VCC), IC43.16 (VCC), IC44.16 (VCC), IC45.20 (VCC), IC46.20 (VCC), IC47.14 (VCC), IC49.20 (VCC), IC50.20 (VCC); also elsewhere on the board
